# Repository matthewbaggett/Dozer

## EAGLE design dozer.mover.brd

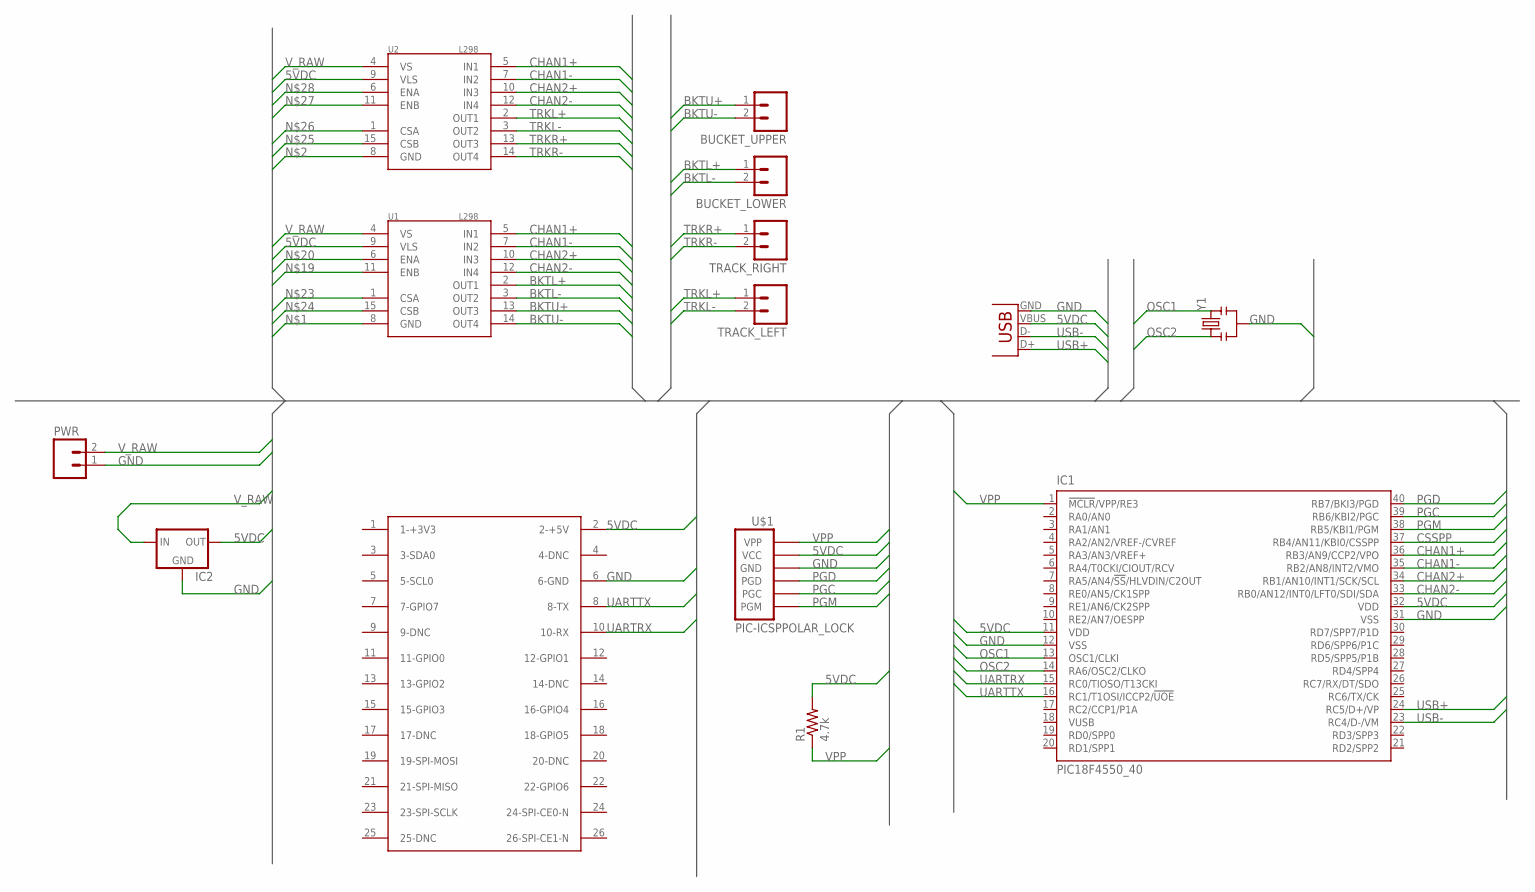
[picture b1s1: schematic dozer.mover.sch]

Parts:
BUCKET_LOWER: M02JST-PTH-2; JST-2-PTH
BUCKET_UPPER: M02JST-PTH-2; JST-2-PTH
IC1: PIC18F4550_40; DIL40
IC2: V_REG_78XXSINK; TO220-IGO
J1: RASPBERRY-PI
JP1: USB-MB-H
PWR: M02JST-PTH-2; JST-2-PTH
R1: 4.7k; AXIAL-0.4
TRACK_LEFT: M02JST-PTH-2; JST-2-PTH
TRACK_RIGHT: M02JST-PTH-2; JST-2-PTH
U1, U2: L298; MULTIWATT15
U$1: PIC-ICSPPOLAR_LOCK; MOLEX-1X6_LOCK
Y1: RESONATORPTH; RESONATOR-PTH

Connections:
5VDC: IC1.11 (VDD), IC1.32 (VDD), IC2.OUT, J1.2 (2-+5V), JP1.VBUS, R1.P$2 (2), U1.9 (VLS), U2.9 (VLS), U$1.5 (VCC)
BKTL+: BUCKET_LOWER.1, U1.2 (OUT1)
BKTL-: BUCKET_LOWER.2, U1.3 (OUT2)
BKTU+: BUCKET_UPPER.1, U1.13 (OUT3)
BKTU-: BUCKET_UPPER.2, U1.14 (OUT4)
CHAN1+: IC1.36 (RB3/AN9/CCP2/VPO), U1.5 (IN1), U2.5 (IN1)
CHAN1-: IC1.35 (RB2/AN8/INT2/VMO), U1.7 (IN2), U2.7 (IN2)
CHAN2+: IC1.34 (RB1/AN10/INT1/SCK/SCL), U1.10 (IN3), U2.10 (IN3)
CHAN2-: IC1.33 (RB0/AN12/INT0/LFT0/SDI/SDA), U1.12 (IN4), U2.12 (IN4)
CSSPP: IC1.37 (RB4/AN11/KBI0/CSSPP)
GND: IC1.12 (VSS), IC1.31 (VSS), IC2.GND, J1.6 (6-GND), JP1.GND, PWR.1, U$1.4 (GND), Y1.2
OSC1: IC1.13 (OSC1/CLKI), Y1.3
OSC2: IC1.14 (RA6/OSC2/CLKO), Y1.1
PGC: IC1.39 (RB6/KBI2/PGC), U$1.2 (PGC)
PGD: IC1.40 (RB7/BKI3/PGD), U$1.3 (PGD)
PGM: IC1.38 (RB5/KBI1/PGM), U$1.1 (PGM)
TRKL+: TRACK_LEFT.1, U2.2 (OUT1)
TRKL-: TRACK_LEFT.2, U2.3 (OUT2)
TRKR+: TRACK_RIGHT.1, U2.13 (OUT3)
TRKR-: TRACK_RIGHT.2, U2.14 (OUT4)
UARTRX: IC1.15 (RC0/TIOSO/T13CKI), J1.10 (10-RX)
UARTTX: IC1.16 (RC1/T1OSI/ICCP2/!UOE), J1.8 (8-TX)
USB+: IC1.24 (RC5/D+/VP), JP1.D+
USB-: IC1.23 (RC4/D-/VM), JP1.D-
VPP: IC1.1 (!MCLR!/VPP/RE3), R1.P$1 (1), U$1.6 (VPP)
V_RAW: IC2.IN, PWR.2, U1.4 (VS), U2.4 (VS)

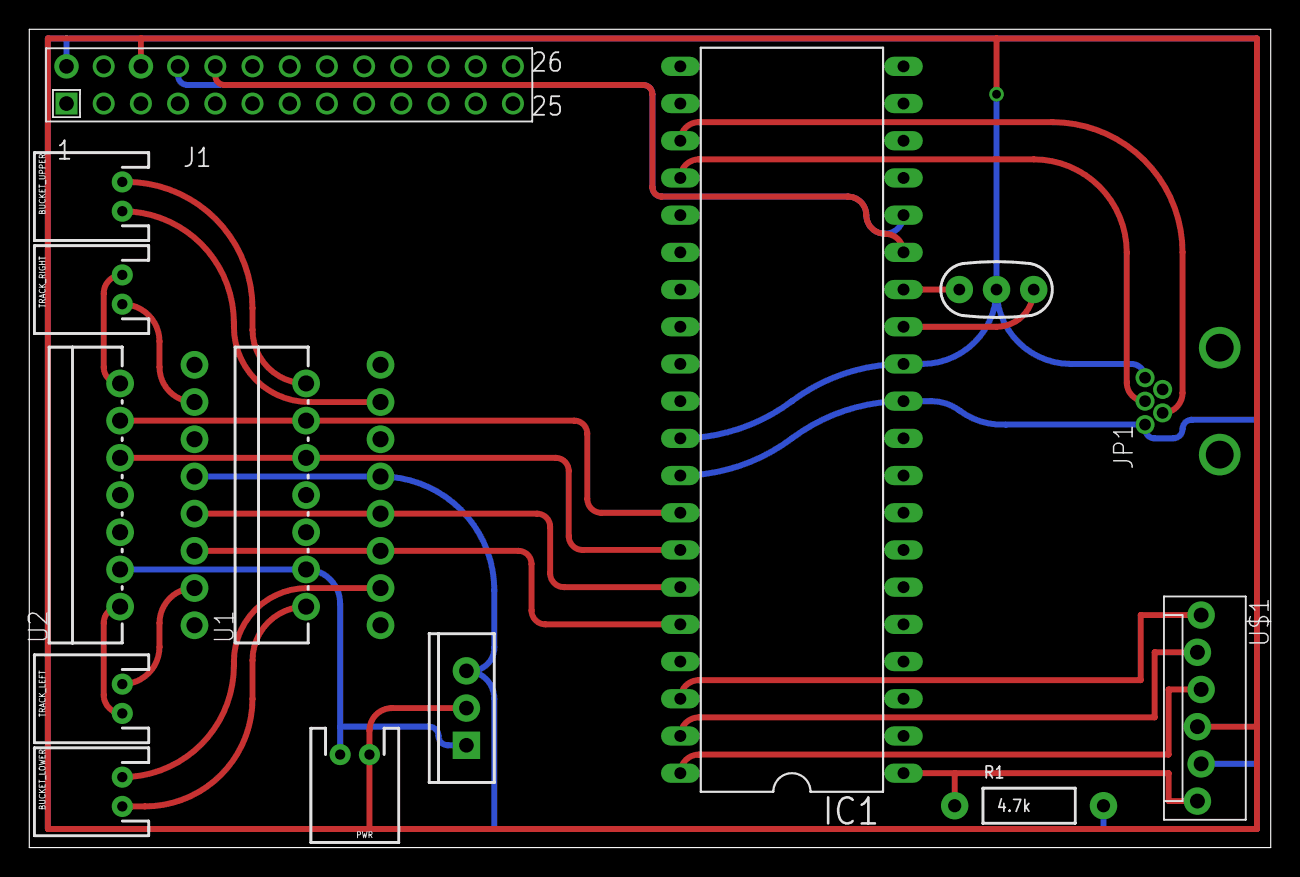
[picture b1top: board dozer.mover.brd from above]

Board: 2 copper layers, 84.8 x 55.9 mm, 14 parts (0 on the bottom side), 25 nets.

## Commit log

2013-10-06 Initial commit of what I have of the Dozer board.
2013-10-06 Updated images, gitignore
2013-10-06 Updated Board to be more elegant
2013-10-06 Renamed parts at Mhisani's behest
2013-10-06 Added beefy 5v vreg for both internal supply and powering the Raspberry Pi
2013-10-06 Migrate motor controls further down interface B, frees up GPIO to use for ICSP without having to add loads of resistors. Also added reset circuit required to make PIC run, but not actually a reset sw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
2013-10-19 reshuffling project so that I can store software in here too
2013-10-19 So this is going to be a learning exercize with you, the reader, and me, the forget-everything-about-C, normally-a-php-developer
2013-10-19 fails to enumerate
2013-10-19 Ffff apparently this wont compile because Windows 8

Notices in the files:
parts and their libraries:
SparkFun-FreqCtrl: Licensing: CC v3.0 Share-Alike You are welcome to use this library for commercial purposes.
